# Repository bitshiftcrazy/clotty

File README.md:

# Clotty

Clotty is a uterus-shaped RP2040 period-tracking companion, sensor board and tiny gaming device.

## What is Clotty?

Clotty is a uterus-shaped, custom RP2040-based hybrid between a sensor board and a gaming device.

She originated from the wish to have an offline-only, privacy-focused period tracker that also happens to gamify the unpleasant, recurrent experience of, well, having a period.

Similar to a Tamagotchi, Clotty accompanies the user (currently: me) throughout the cycle. The goal is to keep her (and ideally myself) alive and happy, while her mood, constitution and little quests change according to the current cycle phase. Some of those quests interact with the physical environment through the board's sensors.

Clotty keeps track of cycle lengths and period dates, but she is **not a medical device** beyond that basic tracking functionality.

Naturally, she runs DOOM as well.

## Current Status

> [!WARNING]
> **Work in progress!**
>
> Clotty is currently at the **first working prototype** stage.
>
> Basic board functionality has been tested and confirmed, but there are known hardware issues and plenty of things I still want to improve.
>
> Please keep that in mind before having this revision fabricated.

Current (basic) bring-up status:

- RP2040 boots and can be flashed
- USB enumerates
- display works
- all three physical buttons work
- both capacitive-touch ovaries work
- temperature sensor works
- ambient-light sensor works
- accelerometer works
- Hall sensor works
- RTC works
- RGB LED works
- LiPo charging works
- basic battery-powered operation works
- DOOM runs
- nothing has exploded (yet)

However, testing is still ongoing! 

## Features

Clotty currently or eventually aims to provide:

- completely offline period tracking
- storage of previous cycle lengths and period dates
- basic prediction of likely future period dates
- cycle-phase-dependent moods
- cycle-phase-dependent quests
- cycle-phase-dependent profound wisdom (eg "everyone hates you" during luteal)
- sensor-based interactions with the environment
- small minigames
- animated Clotty sprites
- RGB cycle-phase indication (menacing menstruation maroon, friendly follicular fuchsia, overjoyed ovulation orchid, looming luteal lava...just examples)
- capacitive-touch ovaries for directional interaction
- battery-powered portable operation
- unreasonable amounts of tiny pixel-art accessories
- DOOM, obviously

## Hardware

Main hardware includes:

- **RP2040** microcontroller
- **W25Q128JVSIQ** 128 Mbit / 16 MiB QSPI flash
- **1.3" 240×240 IPS TFT**, driven by an ST7789
- **RV-8263-C7** real-time clock
- RGB LED
- three physical push buttons
- two capacitive-touch ovaries
- USB-C connector
- LiPo charging and power-management circuitry
- currently a 1,500mAh LiPo

### Sensors

Clotty's sensor selection follows a very scientific design process largely based on "that would be kinda neat".

- **MCP9808-E/MS**: temperature
- **TEMT6000X01**: ambient light
- **LIS3DHTR**: 3-axis accelerometer
- **DRV5032FADBZR**: Hall-effect sensor
- **CAP1203**: capacitive-touch controller for the ovaries

Possible gameplay uses include things like warming Clotty up for a "hot water bottle" quest, putting her somewhere dark for a nap, moving around, or interacting with magnets for no particularly defensible reason.

### Display and Controls

Clotty uses a 240×240 IPS TFT driven by an ST7789.

Controls consist of:

- three physical push buttons
- capacitive-touch ovaries for left and right

The physical buttons are intended mainly for menu navigation and will eventually receive translucent red resin caps shaped like blood drops.

The ovaries are intended for directional or contextual interaction.

Yes, the ovaries also work as controls in DOOM.

### Power

Clotty is designed for portable LiPo-powered operation.

The board includes:

- USB-C input
- LiPo charging
- buck-boost conversion
- power-path / power-selection circuitry
- RTC backup battery

See the schematic for the exact implementation.

## Design

Primarily, the uterus-shape was chosen because it's a period tracking device and subtlety is not exactly my strength.
Periods and reproductive health are still stigmatised too often and Clotty's design is meant to help normalising a biological cycle thanks to which all of us are here in the first place.

But it also turns out that, for reasons nature most likely did not intend, a uterus is surprisingly game-controller-shaped.

The ovaries make convenient touch areas, the centre provides enough room for a display, and the overall shape sits well in the hands.

And yes, the USB-C connector is located at the cervix where it belongs.

Earlier concepts included tampon-shaped and period-pad-shaped devices before the uterus eventually won.

## Known Issues

This revision is a prototype and has known mechanical and layout problems.

Known issues currently include:

- the LiPo JST connector is oriented badly and is difficult to use without brute-forcing the thing in
- the RTC backup battery holder makes the display sit further away from the PCB than intended
- there are currently no proper mounting holes for the planned enclosure (I kinda forgot)
- several component-placement and routing decisions deserve reconsideration (to put it politely)
- mechanical integration with the final case is still unfinished

The board works, but this revision should not be mistaken for a polished production design!

Hardware fixes and cleanup will happen on the `hw-devel` branch before being merged into `main`.

## Fabrication

Fabrication files are available in [`fabrication/`](fabrication/).

The directory contains:

- ready-to-upload Gerber archive
- unpacked Gerbers
- drill files
- JLCPCB BOM
- JLCPCB component-placement file

The current fabrication output corresponds to the prototype revision described above.

Again: **read the Known Issues section before ordering boards.**

## Building / Manufacturing

The project is designed in KiCad.

The repository contains:

- KiCad schematic
- KiCad PCB layout
- project-specific design rules
- local symbol libraries
- local footprint libraries
- artwork used for the PCB
- fabrication output
- schematic PDF

The local libraries are included so the project should not depend on random symbols and footprints disappearing from somewhere on the internet.

If you manufacture this board yourself, verify the BOM, footprints, component availability and fabrication files before ordering. Hardware is unforgiving and I am merely a person on the internet who likes putting USB ports into uteruses.

## Software

Clotty's main application software is still under development and is not yet part of a proper release.
But the firmware will appear in this repo, too.

The planned first usable version includes:

- date and time setup
- entering previous cycle dates / lengths
- entering the current period start date
- simple estimation of the next likely period
- cycle-phase tracking
- animated Clotty states
- small quests
- sensor interactions
- basic menu navigation

The software is deliberately not intended to perform medical analysis!

## DOOM

Clotty can run DOOM.

The DOOM build is based on [`kilograham/rp2040-doom`](https://github.com/kilograham/rp2040-doom).

My Clotty-specific fork lives here:

[`bitshiftcrazy/rp2040-doom`](https://github.com/bitshiftcrazy/rp2040-doom)

For Clotty I replaced the original Pico scanvideo output with a simple blocking SPI backend for the 240×240 ST7789 display and adapted the controls to use the physical buttons and capacitive-touch ovaries.

DOOM renders at 320×200 and is horizontally scaled to 240×200 for the display.

## Repository Structure

```text
.
├── artwork/              PCB artwork and source SVGs
├── docs/                 documentation and schematic PDF
├── fabrication/          Gerbers, BOM and placement files
├── libraries/            project-local KiCad symbols and footprints
├── pics/                 README images
├── clotty.kicad_dru      KiCad design rules
├── clotty.kicad_pcb      PCB layout
├── clotty.kicad_pro      KiCad project
├── clotty.kicad_sch      schematic
├── fp-lib-table
└── sym-lib-table
```

## Documentation

A PDF export of the current schematic can be found here:

[`docs/clotty.pdf`](docs/clotty.pdf)

The full KiCad project is available in the repository root.

More detailed project documentation, design background and development notes will also be published on my blog:

[missmolerat.com](https://missmolerat.com/)

## Roadmap

Roughly:

- fix JST placement
- improve RTC backup-battery placement
- add proper enclosure mounting points
- clean up placement and routing
- design the enclosure
- finish the first actual Clotty application
- add cycle-phase logic
- add quests and sensor interactions
- make far too many sprites
- design resin blood-drop button caps
- continue finding increasingly unnecessary things for a uterus to do

## License

- hardware design files: **CERN Open Hardware Licence Version 2 – Strongly Reciprocal (CERN-OHL-S-2.0)**
- original artwork and documentation: **CC BY-SA 4.0**

DOOM itself and the Clotty DOOM fork are not covered by the hardware licence of this repository.

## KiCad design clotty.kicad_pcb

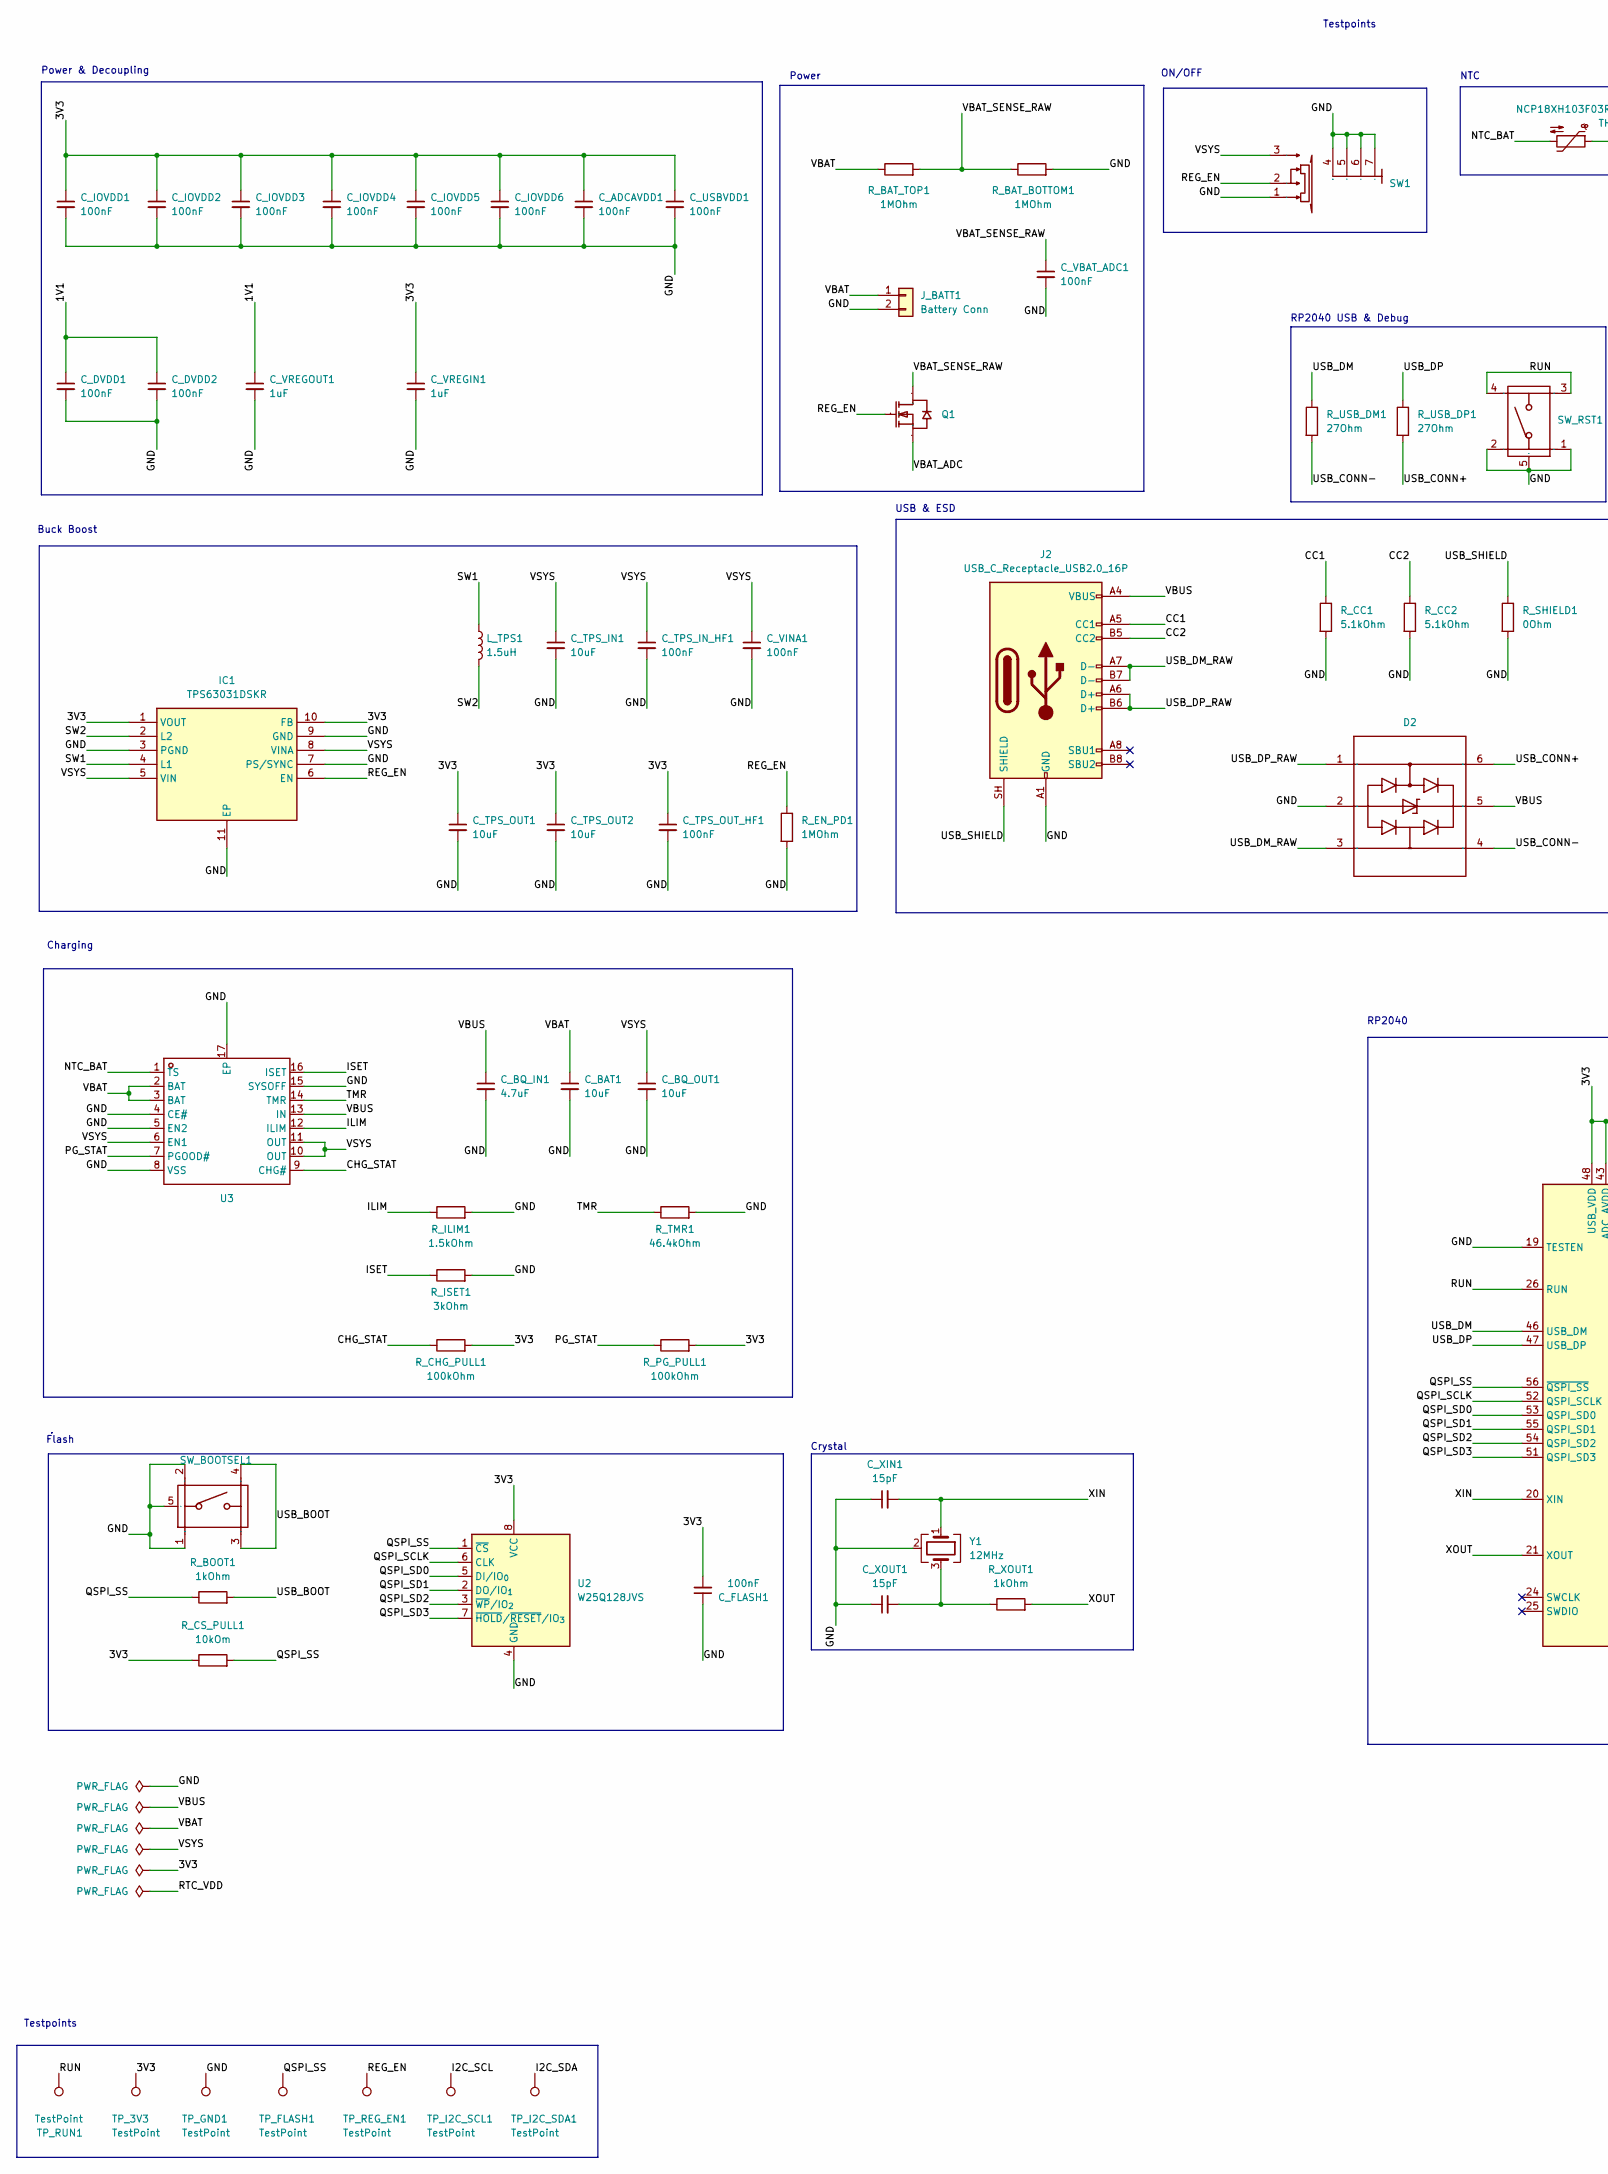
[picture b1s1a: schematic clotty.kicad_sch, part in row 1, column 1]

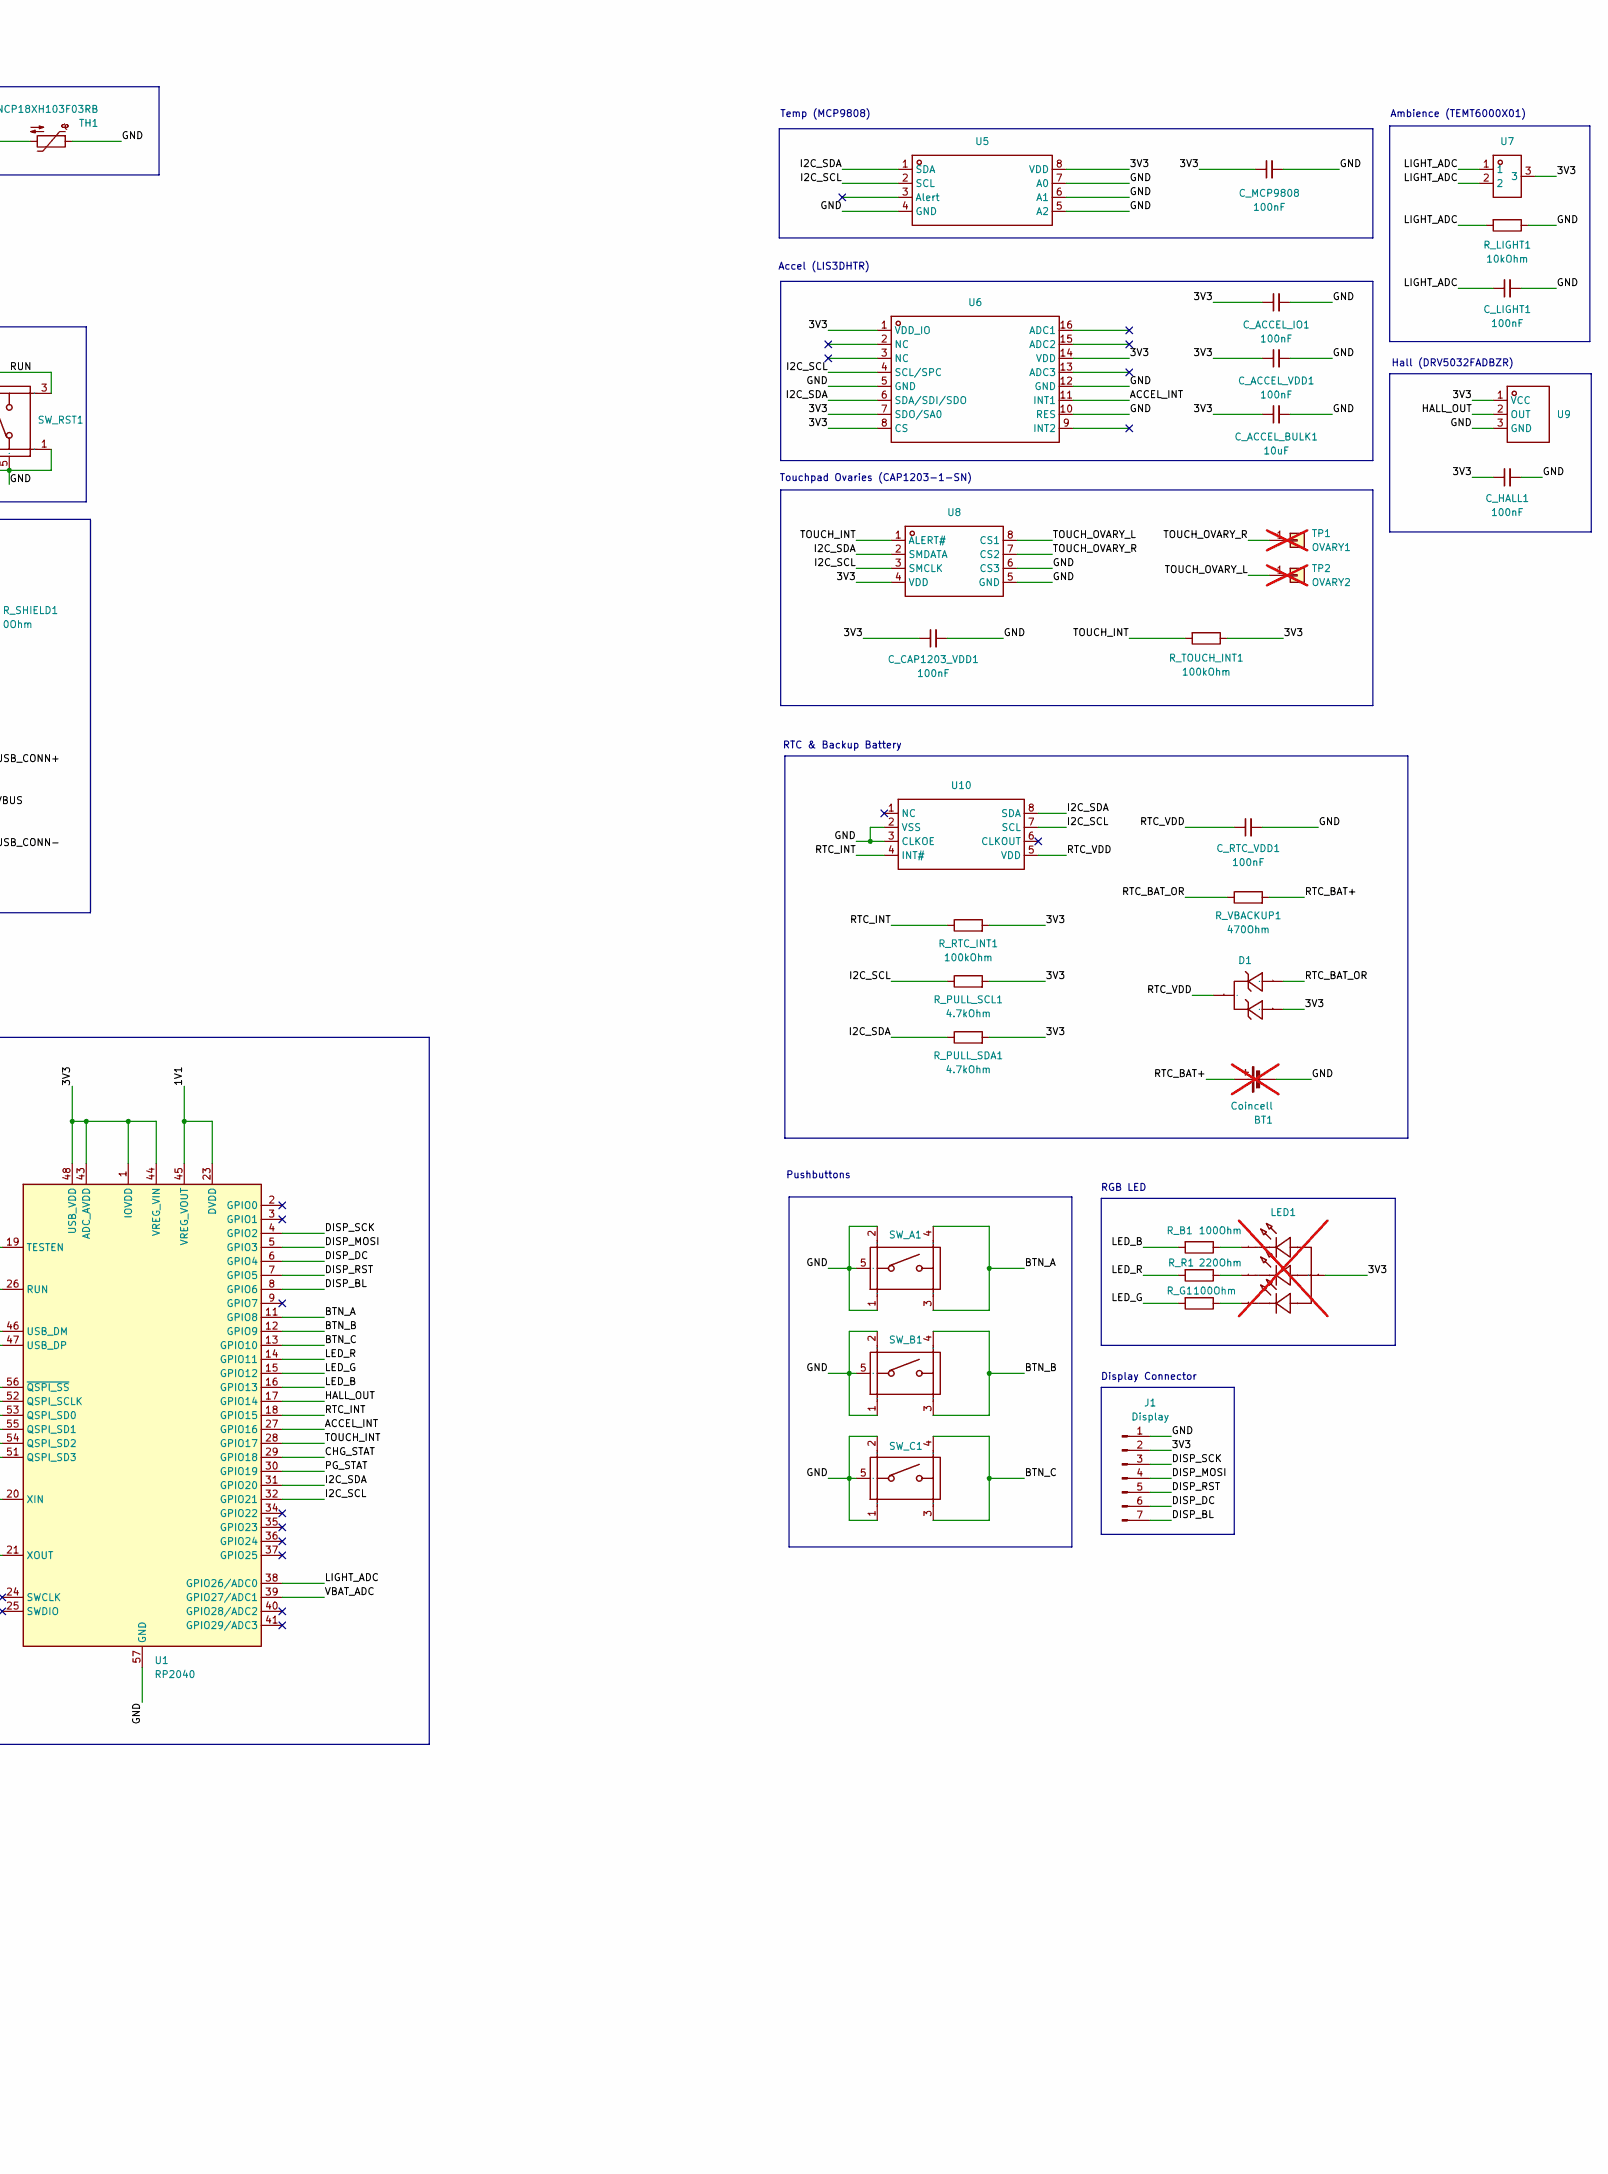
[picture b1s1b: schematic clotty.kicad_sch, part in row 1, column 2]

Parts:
BT1: Coincell; BAT-SMD_KEYSTONE-1056; not fitted
C_ACCEL_BULK1: 10uF; C_0805_2012Metric
C_ACCEL_IO1: 100nF; C_0603_1608Metric
C_ACCEL_VDD1: 100nF; C_0603_1608Metric
C_ADCAVDD1: 100nF; C_0603_1608Metric
C_BAT1: 10uF; C_0805_2012Metric
C_BQ_IN1: 4.7uF; C_0805_2012Metric
C_BQ_OUT1: 10uF; C_0805_2012Metric
C_CAP1203_VDD1: 100nF; C_0603_1608Metric
C_DVDD1, C_DVDD2: 100nF; C_0603_1608Metric
C_FLASH1: 100nF; C_0603_1608Metric
C_HALL1: 100nF; C_0603_1608Metric
C_IOVDD1, C_IOVDD2, C_IOVDD3, C_IOVDD4, C_IOVDD5, C_IOVDD6: 100nF; C_0603_1608Metric
C_LIGHT1: 100nF; C_0603_1608Metric
C_MCP9808: 100nF; C_0603_1608Metric
C_RTC_VDD1: 100nF; C_0603_1608Metric
C_TPS_IN1: 10uF; C_0805_2012Metric
C_TPS_IN_HF1: 100nF; C_0603_1608Metric
C_TPS_OUT1, C_TPS_OUT2: 10uF; C_0805_2012Metric
C_TPS_OUT_HF1: 100nF; C_0603_1608Metric
C_USBVDD1: 100nF; C_0603_1608Metric
C_VBAT_ADC1: 100nF; C_0603_1608Metric
C_VINA1: 100nF; C_0603_1608Metric
C_VREGIN1: 1uF; C_0603_1608Metric
C_VREGOUT1: 1uF; C_0603_1608Metric
C_XIN1: 15pF; C_0603_1608Metric
C_XOUT1: 15pF; C_0603_1608Metric
D1: SOT-23-3_L2.9-W1.3-P1.90-LS2.4-BR; Manufacturer Part BAS70-05,215; LCSC Part Name 电压:70V 电流:70mA
D2: SOT-666-6_L1.6-W1.2-P0.50-LS1.6-BR; Manufacturer Part USBLC6-2P6; LCSC Part Name 单向ESD 5.25V截止 峰值脉冲电流：5A@8/20us
IC1: TPS63031DSKR; SON-10_L2.5-W2.5-P0.50-TL-EP; Mouser Part Number 595-TPS63031DSKR
J1: Display; PinHeader_1x07_P2.54mm_Vertical
J2: USB_C_Receptacle_USB2.0_16P; USB_C_Receptacle_GCT_USB4105-xx-A_16P_TopMnt_Horizontal; LCSC Part # C3020560
J_BATT1: Battery Conn; CONN-SMD_P2.00_S2B-PH-SM4-TB-LF-SN; LCSC Part # C295747
LED1: LED-SMD_4P-L3.2-W2.8-LS3.5-TR_150141M173100; Manufacturer Part 150141M173100; LCSC Part Name SMT全彩顶部发光LED; not fitted
L_TPS1: 1.5uH; IND-SMD_L4.5-W4.1_SRP4020TA
Q1: SOT-23-3_L2.9-W1.6-P1.90-LS2.8-BR; Manufacturer Part DMN2056U-7; LCSC Part Name 1个N沟道 耐压:20V 电流:4A
R_B1: 100Ohm; R_0603_1608Metric
R_BAT_BOTTOM1: 1MOhm; R_0603_1608Metric
R_BAT_TOP1: 1MOhm; R_0603_1608Metric
R_BOOT1: 1kOhm; R_0603_1608Metric
R_CC1, R_CC2: 5.1kOhm; R_0603_1608Metric
R_CHG_PULL1: 100kOhm; R_0603_1608Metric
R_CS_PULL1: 10kOm; R_0603_1608Metric
R_EN_PD1: 1MOhm; R_0603_1608Metric
R_G1: 100Ohm; R_0603_1608Metric
R_ILIM1: 1.5kOhm; R_0603_1608Metric
R_ISET1: 3kOhm; R_0603_1608Metric
R_LIGHT1: 10kOhm; R_0603_1608Metric
R_PG_PULL1: 100kOhm; R_0603_1608Metric
R_PULL_SCL1: 4.7kOhm; R_0603_1608Metric
R_PULL_SDA1: 4.7kOhm; R_0603_1608Metric
R_R1: 220Ohm; R_0603_1608Metric
R_RTC_INT1: 100kOhm; R_0603_1608Metric
R_SHIELD1: 0Ohm; R_0603_1608Metric
R_TMR1: 46.4kOhm; R_0603_1608Metric
R_TOUCH_INT1: 100kOhm; R_0603_1608Metric
R_USB_DM1: 27Ohm; R_0603_1608Metric
R_USB_DP1: 27Ohm; R_0603_1608Metric
R_VBACKUP1: 470Ohm; R_0603_1608Metric
R_XOUT1: 1kOhm; R_0603_1608Metric
SW1: SW-SMD_SSSS811101; Manufacturer Part SSSS811101; LCSC Part Name 1.4mm厚、1.5/2.0mm行程的表面贴装型开关
SW_A1: KEY-SMD_KMR2XXGXXX; Manufacturer Part KMR221GLFS; LCSC Part Name 4.6*2.8*1.9mm 立贴 轻触开关
SW_B1: KEY-SMD_KMR2XXGXXX; Manufacturer Part KMR221GLFS; LCSC Part Name 4.6*2.8*1.9mm 立贴 轻触开关
SW_BOOTSEL1: KEY-SMD_KMR2XXGXXX; Manufacturer Part KMR221GLFS; LCSC Part Name 4.6*2.8*1.9mm 立贴 轻触开关
SW_C1: KEY-SMD_KMR2XXGXXX; Manufacturer Part KMR221GLFS; LCSC Part Name 4.6*2.8*1.9mm 立贴 轻触开关
SW_RST1: KEY-SMD_KMR2XXGXXX; Manufacturer Part KMR221GLFS; LCSC Part Name 4.6*2.8*1.9mm 立贴 轻触开关
TH1: NCP18XH103F03RB; R0603; LCSC Part # C13564
TP1: OVARY1; ovary_left; not fitted
TP2: OVARY2; ovary_right; not fitted
TP_3V3: TestPoint; TestPoint_Pad_1.5x1.5mm
TP_FLASH1: TestPoint; TestPoint_Pad_1.0x1.0mm
TP_GND1: TestPoint; TestPoint_Pad_1.5x1.5mm
TP_I2C_SCL1, TP_I2C_SDA1: TestPoint; TestPoint_Pad_1.0x1.0mm
TP_REG_EN1: TestPoint; TestPoint_Pad_1.0x1.0mm
TP_RUN1: TestPoint; TestPoint_Pad_1.0x1.0mm
U1: RP2040; QFN-56-1EP_7x7mm_P0.4mm_EP3.2x3.2mm; LCSC Part # C2040
U2: W25Q128JVS; SOIC-8_5.3x5.3mm_P1.27mm; LCSC Part # C97521
U3: VQFN-16_L3.0-W3.0-P0.50-TL-EP1.7; Manufacturer Part BQ24075RGTT; LCSC Part Name 具有电源路径的独立型单芯线性电池充电器
U5: MSOP-8_L3.0-W3.0-P0.65-LS4.9-BL; Manufacturer Part MCP9808-E/MS; LCSC Part Name ±0.5°C最高精度数字温度传感器
U6: LGA-16_L3.0-W3.0-P0.50-TL; Manufacturer Part LIS3DHTR; LCSC Part Name MEMS数字输出运动传感器：超低功耗、高性能三轴加速度计
U7: SENSORS-SMD_TEMT6000X01; Manufacturer Part TEMT6000X01; LCSC Part Name TEMT6000X01
U8: SOIC-8_L5.0-W4.0-P1.27-LS6.0-BL; Manufacturer Part CAP1203-1-SN; LCSC Part Name CAP1203 1 SN
U9: SOT-23-3_L2.9-W1.3-P0.95-LS2.4-BR; Manufacturer Part DRV5032FADBZR; LCSC Part Name 数字锁存霍尔效应传感器
U10: DFN-8_L3.2-W1.5-P0.9-BL; Manufacturer Part RV-8263-C7-32.768KHZ-20PPM-TA-QA; LCSC Part Name 带 I2C 总线的实时时钟模块
Y1: 12MHz; CRYSTAL-SMD_4P-L3.2-W2.5-BL; LCSC Part # C20625731

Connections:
/1V1: C_DVDD1.1, C_DVDD2.1, C_VREGOUT1.1, U1.23 (DVDD), U1.45 (VREG_VOUT), U1.50 (DVDD)
/3V3: C_ACCEL_BULK1.1, C_ACCEL_IO1.1, C_ACCEL_VDD1.1, C_ADCAVDD1.1, C_CAP1203_VDD1.1, C_FLASH1.2, C_HALL1.1, C_IOVDD1.1, C_IOVDD2.1, C_IOVDD3.1, C_IOVDD4.1, C_IOVDD5.1, C_IOVDD6.1, C_MCP9808.1, C_TPS_OUT1.1, C_TPS_OUT2.1, C_TPS_OUT_HF1.1, C_USBVDD1.1, C_VREGIN1.1, D1.1 (A), IC1.1 (VOUT), IC1.10 (FB), J1.2, LED1.1 (+), R_CHG_PULL1.2, R_CS_PULL1.1, R_PG_PULL1.2, R_PULL_SCL1.2, R_PULL_SDA1.2, R_RTC_INT1.2, R_TOUCH_INT1.1, TP_3V3.1 (1_1), U1.1 (IOVDD), U1.10 (IOVDD), U1.22 (IOVDD), U1.33 (IOVDD), U1.42 (IOVDD), U1.43 (ADC_AVDD), U1.44 (VREG_VIN), U1.48 (USB_VDD), U1.49 (IOVDD), U2.8 (VCC), U5.8 (VDD), U6.1 (VDD_IO), U6.7 (SDO/SA0), U6.8 (CS), U6.14 (VDD), U7.3, U8.4 (VDD), U9.1 (VCC)
/ACCEL_INT: U1.27 (GPIO16), U6.11 (INT1)
/BTN_A: SW_A1.3, SW_A1.4, U1.11 (GPIO8)
/BTN_B: SW_B1.3, SW_B1.4, U1.12 (GPIO9)
/BTN_C: SW_C1.3, SW_C1.4, U1.13 (GPIO10)
/CC1: J2.A5 (CC1), R_CC1.1
/CC2: J2.B5 (CC2), R_CC2.1
/CHG_STAT: R_CHG_PULL1.1, U1.29 (GPIO18), U3.9 (CHG#)
/DISP_BL: J1.7, U1.8 (GPIO6)
/DISP_DC: J1.6, U1.6 (GPIO4)
/DISP_MOSI: J1.4, U1.5 (GPIO3)
/DISP_RST: J1.5, U1.7 (GPIO5)
/DISP_SCK: J1.3, U1.4 (GPIO2)
/GND: BT1.2 (-), C_ACCEL_BULK1.2, C_ACCEL_IO1.2, C_ACCEL_VDD1.2, C_ADCAVDD1.2, C_BAT1.2, C_BQ_IN1.2, C_BQ_OUT1.2, C_CAP1203_VDD1.2, C_DVDD1.2, C_DVDD2.2, C_FLASH1.1, C_HALL1.2, C_IOVDD1.2, C_IOVDD2.2, C_IOVDD3.2, C_IOVDD4.2, C_IOVDD5.2, C_IOVDD6.2, C_LIGHT1.2, C_MCP9808.2, C_RTC_VDD1.2, C_TPS_IN1.2, C_TPS_IN_HF1.2, C_TPS_OUT1.2, C_TPS_OUT2.2, C_TPS_OUT_HF1.2, C_USBVDD1.2, C_VBAT_ADC1.2, C_VINA1.2, C_VREGIN1.2, C_VREGOUT1.2, C_XIN1.1, C_XOUT1.1, D2.2 (GND), IC1.3 (PGND), IC1.7 (PS/SYNC), IC1.9 (GND), IC1.11 (EP), J1.1, J2.A1 (GND), J2.A12 (GND), J2.B1 (GND), J2.B12 (GND), J_BATT1.2, R_BAT_BOTTOM1.2, R_CC1.2, R_CC2.2, R_EN_PD1.2, R_ILIM1.2, R_ISET1.2, R_LIGHT1.1, R_SHIELD1.2, R_TMR1.2, SW1.1, SW1.4, SW1.5, SW1.6, SW1.7, SW_A1.1, SW_A1.2, SW_A1.5, SW_B1.1, SW_B1.2, SW_B1.5, SW_BOOTSEL1.1, SW_BOOTSEL1.2, SW_BOOTSEL1.5, SW_C1.1, SW_C1.2, SW_C1.5, SW_RST1.1, SW_RST1.2, SW_RST1.5, TH1.1, TP_GND1.1 (1_1), U1.19 (TESTEN), U1.57 (GND), U2.4 (GND), U3.4 (CE#), U3.5 (EN2), U3.8 (VSS), U3.15 (SYSOFF), U3.17 (EP), U5.4 (GND), U5.5 (A2), U5.6 (A1), U5.7 (A0), U6.5 (GND), U6.10 (RES), U6.12 (GND), U8.5 (GND), U8.6 (CS3), U9.3 (GND), U10.2 (VSS), U10.3 (CLKOE), Y1.2 (G), Y1.4 (G)
/HALL_OUT: U1.17 (GPIO14), U9.2 (OUT)
/I2C_SCL: R_PULL_SCL1.1, TP_I2C_SCL1.1 (1_1), U1.32 (GPIO21), U5.2 (SCL), U6.4 (SCL/SPC), U8.3 (SMCLK), U10.7 (SCL)
/I2C_SDA: R_PULL_SDA1.1, TP_I2C_SDA1.1 (1_1), U1.31 (GPIO20), U5.1 (SDA), U6.6 (SDA/SDI/SDO), U8.2 (SMDATA), U10.8 (SDA)
/ILIM: R_ILIM1.1, U3.12 (ILIM)
/ISET: R_ISET1.1, U3.16 (ISET)
/LED_B: R_B1.2, U1.16 (GPIO13)
/LED_G: R_G1.2, U1.15 (GPIO12)
/LED_R: R_R1.2, U1.14 (GPIO11)
/LIGHT_ADC: C_LIGHT1.1, R_LIGHT1.2, U1.38 (GPIO26/ADC0), U7.1, U7.2
/NTC_BAT: TH1.2, U3.1 (TS)
/PG_STAT: R_PG_PULL1.1, U1.30 (GPIO19), U3.7 (PGOOD#)
/QSPI_SCLK: U1.52 (QSPI_SCLK), U2.6 (CLK)
/QSPI_SD0: U1.53 (QSPI_SD0), U2.5 (DI/IO_{0})
/QSPI_SD1: U1.55 (QSPI_SD1), U2.2 (DO/IO_{1})
/QSPI_SD2: U1.54 (QSPI_SD2), U2.3 (~WP/IO_{2})
/QSPI_SD3: U1.51 (QSPI_SD3), U2.7 (~HOLD/~RESET/IO_{3})
/QSPI_SS: R_BOOT1.1, R_CS_PULL1.2, TP_FLASH1.1 (1_1), U1.56 (~QSPI_SS), U2.1 (~CS)
/REG_EN: IC1.6 (EN), Q1.1 (G), R_EN_PD1.1, SW1.2, TP_REG_EN1.1 (1_1)
/RTC_BAT+: BT1.1 (+), R_VBACKUP1.2
/RTC_BAT_OR: D1.2 (A), R_VBACKUP1.1
/RTC_INT: R_RTC_INT1.1, U1.18 (GPIO15), U10.4 (INT#)
/RTC_VDD: C_RTC_VDD1.1, D1.3 (C), U10.5 (VDD)
/RUN: SW_RST1.3, SW_RST1.4, TP_RUN1.1 (1_1), U1.26 (RUN)
/SW1: IC1.4 (L1), L_TPS1.1
/SW2: IC1.2 (L2), L_TPS1.2
/TMR: R_TMR1.1, U3.14 (TMR)
/TOUCH_INT: R_TOUCH_INT1.2, U1.28 (GPIO17), U8.1 (ALERT#)
/TOUCH_OVARY_L: TP2.1 (Pin_1_1), U8.8 (CS1)
/TOUCH_OVARY_R: TP1.1 (Pin_1_1), U8.7 (CS2)
/USB_BOOT: R_BOOT1.2, SW_BOOTSEL1.3, SW_BOOTSEL1.4
/USB_CONN+: D2.6 (I/O1), R_USB_DP1.2
/USB_CONN-: D2.4 (I/O2), R_USB_DM1.2
/USB_DM: R_USB_DM1.1, U1.46 (USB_DM)
/USB_DM_RAW: D2.3 (I/O2), J2.A7 (D-), J2.B7 (D-)
/USB_DP: R_USB_DP1.1, U1.47 (USB_DP)
/USB_DP_RAW: D2.1 (I/O1), J2.A6 (D+), J2.B6 (D+)
/USB_SHIELD: J2.SH (SHIELD), R_SHIELD1.1
/VBAT: C_BAT1.1, J_BATT1.1, R_BAT_TOP1.1, U3.2 (BAT), U3.3 (BAT)
/VBAT_ADC: Q1.2 (S), U1.39 (GPIO27/ADC1)
/VBAT_SENSE_RAW: C_VBAT_ADC1.1, Q1.3 (D), R_BAT_BOTTOM1.1, R_BAT_TOP1.2
/VBUS: C_BQ_IN1.1, D2.5 (VBUS), J2.A4 (VBUS), J2.A9 (VBUS), J2.B4 (VBUS), J2.B9 (VBUS), U3.13 (IN)
/VSYS: C_BQ_OUT1.1, C_TPS_IN1.1, C_TPS_IN_HF1.1, C_VINA1.1, IC1.5 (VIN), IC1.8 (VINA), SW1.3, U3.6 (EN1), U3.10 (OUT), U3.11 (OUT)
/XIN: C_XIN1.2, U1.20 (XIN), Y1.1
/XOUT: R_XOUT1.2, U1.21 (XOUT)
unnamed: C_XOUT1.2, R_XOUT1.1, Y1.3
unnamed: LED1.2 (-), R_B1.1
unnamed: LED1.3 (-), R_R1.1
unnamed: LED1.4 (-), R_G1.1

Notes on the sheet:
Crystal
Testpoints
Flash
USB & ESD
Charging
Buck Boost
RP2040
Display Connector
Touchpad Ovaries (CAP1203-1-SN)
Temp (MCP9808)
Hall (DRV5032FADBZR)
ON/OFF
NTC
Power
Pushbuttons
RGB LED
Accel (LIS3DHTR)
Power & Decoupling
Ambience (TEMT6000X01)
RP2040 USB & Debug
RTC & Backup Battery

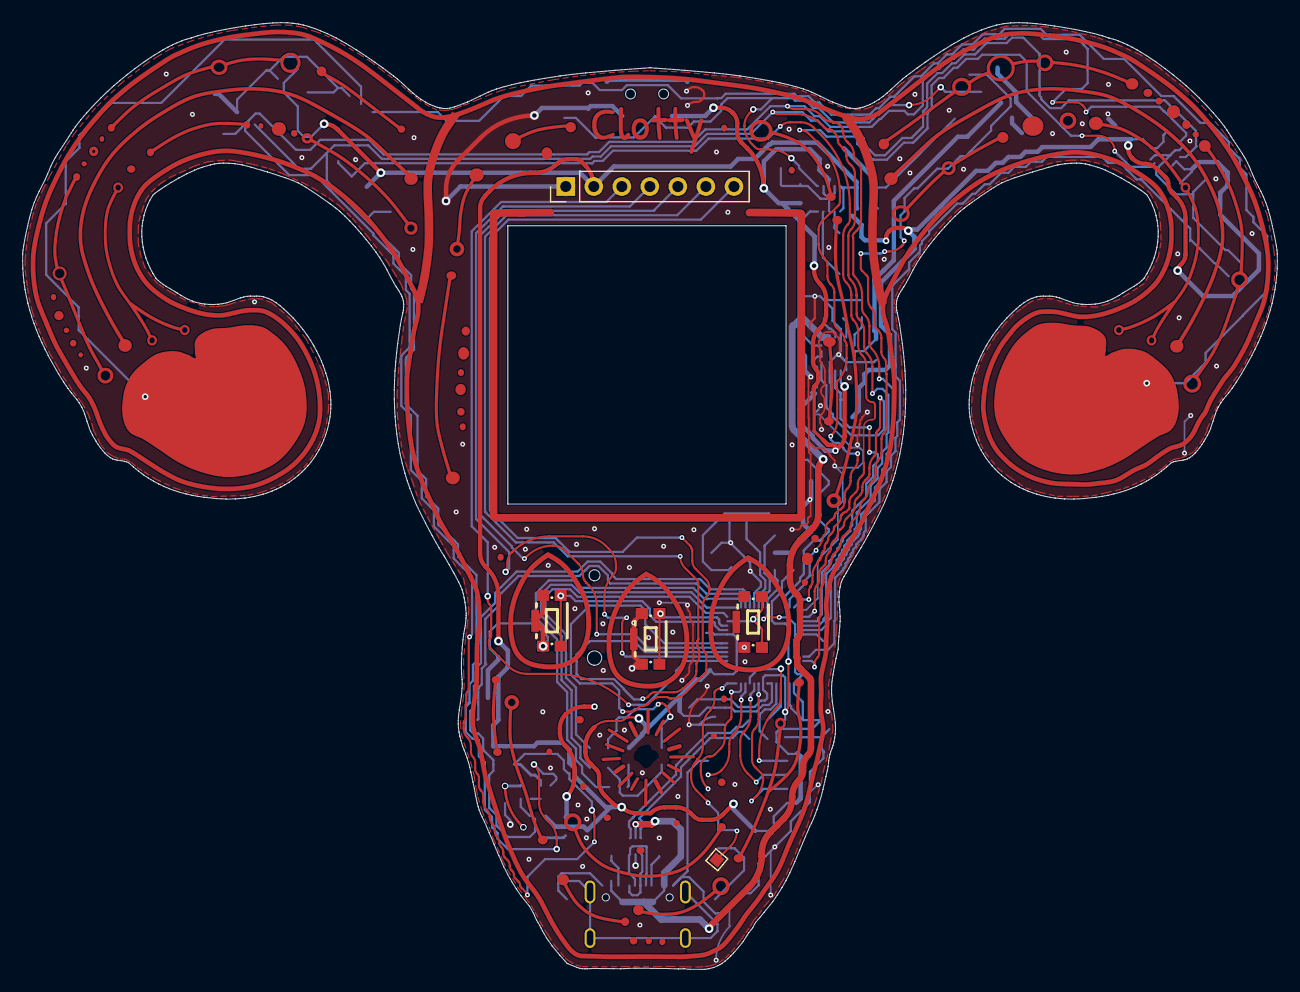
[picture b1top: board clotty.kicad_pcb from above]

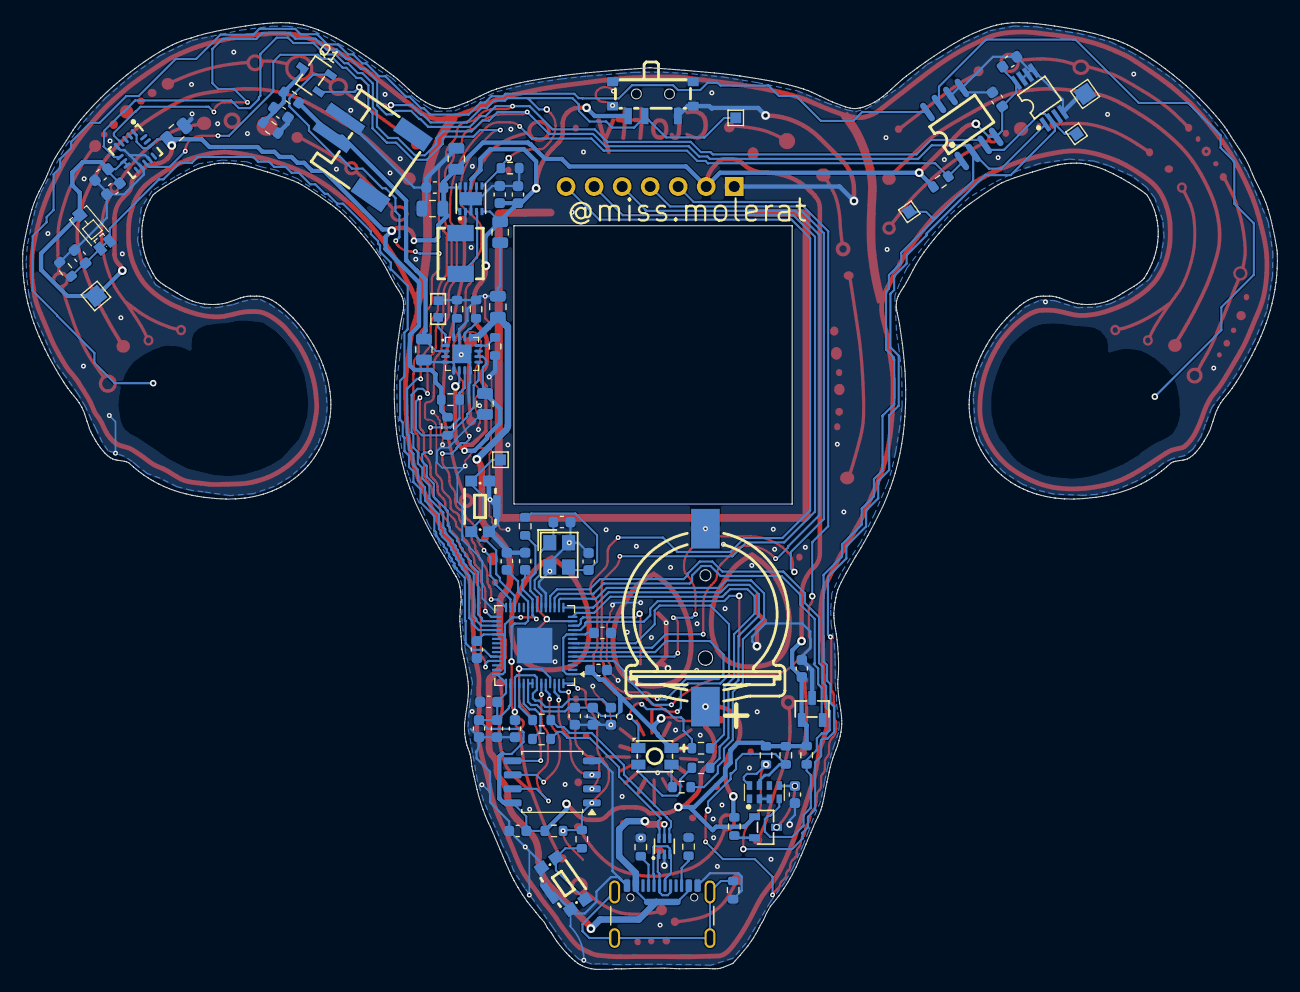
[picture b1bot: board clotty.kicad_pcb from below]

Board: 2 copper layers, 113.7 x 85.8 mm, 94 parts (87 on the bottom side), 63 nets.
